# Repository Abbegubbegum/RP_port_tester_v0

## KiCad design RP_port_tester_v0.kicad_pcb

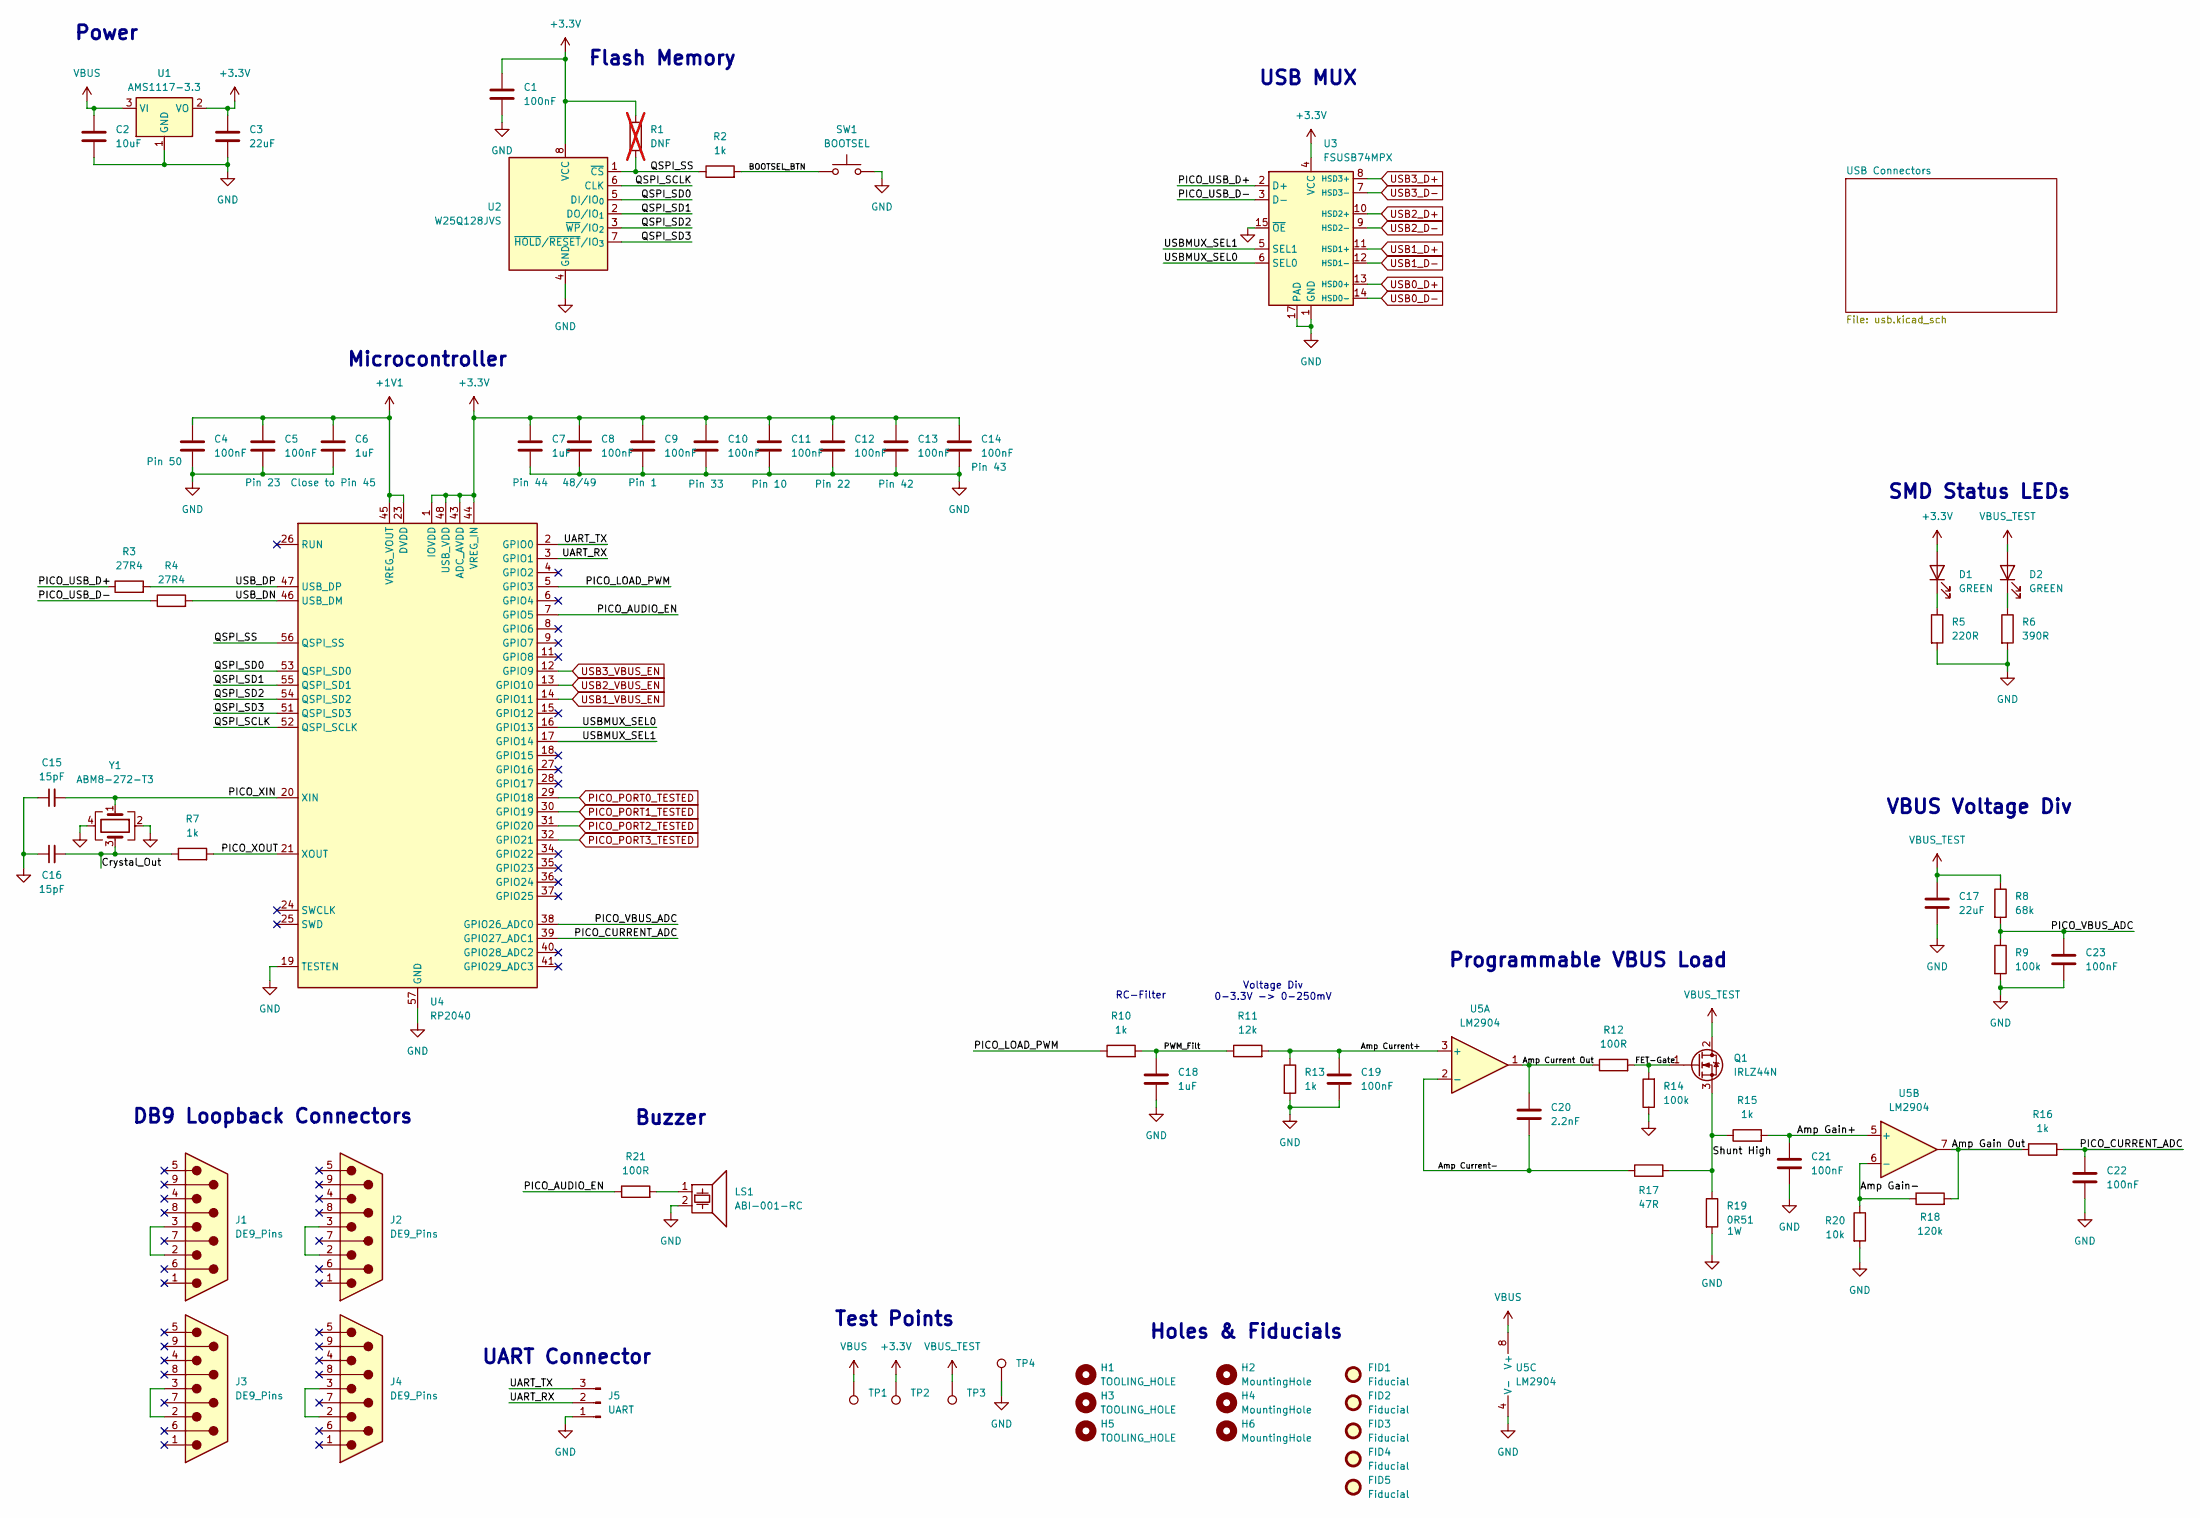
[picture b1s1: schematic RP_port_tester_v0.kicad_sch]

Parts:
C1, C4, C5, C8, C9, C10, C11, C12, C13, C14, C19, C21, C22, C23: 100nF; C_0603_1608Metric_Pad1.08x0.95mm_HandSolder
C2: 10uF; C_1206_3216Metric_Pad1.33x1.80mm_HandSolder
C3, C17: 22uF; C_1206_3216Metric_Pad1.33x1.80mm_HandSolder
C6, C7, C18: 1uF; C_0603_1608Metric_Pad1.08x0.95mm_HandSolder
C15, C16: 15pF; C_0402_1005Metric_Pad0.74x0.62mm_HandSolder
C20: 2.2nF; C_0402_1005Metric_Pad0.74x0.62mm_HandSolder
D1, D2: GREEN; D_0805_2012Metric_Pad1.15x1.40mm_HandSolder
FID1, FID2, FID3, FID4, FID5: Fiducial; Fiducial_1mm_Mask2mm
H1, H3, H5: TOOLING_HOLE; ToolingHole_1.152mm
H2, H4, H6: MountingHole; MountingHole_3.2mm_M3
J1, J2, J3, J4: DE9_Pins; DB9_Horizontal
J5: UART; PinHeader_1x03_P2.54mm_Vertical
LS1: ABI-001-RC; Buzzer_15x7.5RM7.6
Q1: IRLZ44N; TO-220-3_Horizontal_TabDown
R1: DNF; R_0603_1608Metric_Pad0.98x0.95mm_HandSolder; not fitted
R2, R7, R10, R13, R15, R16: 1k; R_0603_1608Metric_Pad0.98x0.95mm_HandSolder
R3, R4: 27R4; R_0603_1608Metric_Pad0.98x0.95mm_HandSolder
R5: 220R; R_0603_1608Metric_Pad0.98x0.95mm_HandSolder
R6: 390R; R_0603_1608Metric_Pad0.98x0.95mm_HandSolder
R8: 68k; R_0603_1608Metric_Pad0.98x0.95mm_HandSolder
R9, R14: 100k; R_0603_1608Metric_Pad0.98x0.95mm_HandSolder
R11: 12k; R_0603_1608Metric_Pad0.98x0.95mm_HandSolder
R12, R21: 100R; R_0603_1608Metric_Pad0.98x0.95mm_HandSolder
R17: 47R; R_0603_1608Metric_Pad0.98x0.95mm_HandSolder
R18: 120k; R_0603_1608Metric_Pad0.98x0.95mm_HandSolder
R19: 0R51; R_Axial_DIN0309_L9.0mm_D3.2mm_P15.24mm_Horizontal
R20: 10k; R_0603_1608Metric_Pad0.98x0.95mm_HandSolder
SW1: BOOTSEL; SW_SPST_PTS645Sx43SMTR92
TP1, TP2, TP3, TP4: TestPoint; TestPoint_Plated_Hole_D2.0mm
U1: AMS1117-3.3; SOT-223-3_TabPin2
U2: W25Q128JVS; SOIC-8_5.3x5.3mm_P1.27mm
U3: FSUSB74MPX; QFN-16-1EP_3x3mm_P0.5mm_EP1.7x1.7mm_ThermalVias
U4: RP2040; QFN-56-1EP_7x7mm_P0.4mm_EP3.2x3.2mm_ThermalVias
U5: LM2904; DIP-8_W7.62mm
Y1: ABM8-272-T3; Crystal_SMD_Abracon_ABM8G-4Pin_3.2x2.5mm

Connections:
+1V1: C4.1, C5.1, C6.1, U4.23 (DVDD), U4.45 (VREG_VOUT), U4.50 (DVDD)
+3.3V: C1.1, C3.1, C7.1, C8.1, C9.1, C10.1, C11.1, C12.1, C13.1, C14.1, D1.2 (A), R1.1, TP2.1, U1.2 (VO), U2.8 (VCC), U3.4 (VCC), U4.1 (IOVDD), U4.10 (IOVDD), U4.22 (IOVDD), U4.33 (IOVDD), U4.42 (IOVDD), U4.43 (ADC_AVDD), U4.44 (VREG_IN), U4.48 (USB_VDD), U4.49 (IOVDD)
/Amp Current Out: C20.1, R12.1, U5.1
/Amp Current+: C19.1, R11.2, R13.1, U5.3 (+)
/Amp Current-: C20.2, R17.1, U5.2 (-)
/Amp Gain Out: R16.1, R18.2, U5.7
/Amp Gain+: C21.1, R15.2, U5.5 (+)
/Amp Gain-: R18.1, R20.1, U5.6 (-)
/BOOTSEL_BTN: R2.2, SW1.1
/Crystal_Out: C16.2, R7.1, Y1.3
/FET-Gate: Q1.1 (G), R12.2, R14.2
/PICO_AUDIO_EN: R21.1, U4.7 (GPIO5)
/PICO_CURRENT_ADC: C22.1, R16.2, U4.39 (GPIO27_ADC1)
/PICO_LOAD_PWM: R10.1, U4.5 (GPIO3)
/PICO_USB_D+: R3.1, U3.2 (D+)
/PICO_USB_D-: R4.1, U3.3 (D-)
/PICO_VBUS_ADC: C23.1, R8.2, R9.1, U4.38 (GPIO26_ADC0)
/PICO_XIN: C15.2, U4.20 (XIN), Y1.1
/PICO_XOUT: R7.2, U4.21 (XOUT)
/PWM_Filt: C18.1, R10.2, R11.1
/QSPI_SCLK: U2.6 (CLK), U4.52 (QSPI_SCLK)
/QSPI_SD0: U2.5 (DI/IO_{0}), U4.53 (QSPI_SD0)
/QSPI_SD1: U2.2 (DO/IO_{1}), U4.55 (QSPI_SD1)
/QSPI_SD2: U2.3 (~WP/IO_{2}), U4.54 (QSPI_SD2)
/QSPI_SD3: U2.7 (~HOLD/~RESET/IO_{3}), U4.51 (QSPI_SD3)
/QSPI_SS: R1.2, R2.1, U2.1 (~CS), U4.56 (QSPI_SS)
/Shunt High: Q1.3 (S), R15.1, R17.2, R19.1
/UART_RX: J5.2, U4.3 (GPIO1)
/UART_TX: J5.3, U4.2 (GPIO0)
/USBMUX_SEL0: U3.6 (SEL0), U4.16 (GPIO13)
/USBMUX_SEL1: U3.5 (SEL1), U4.17 (GPIO14)
/USB_DN: R4.2, U4.46 (USB_DM)
/USB_DP: R3.2, U4.47 (USB_DP)
GND: C1.2, C2.2, C3.2, C4.2, C5.2, C6.2, C7.2, C8.2, C9.2, C10.2, C11.2, C12.2, C13.2, C14.2, C15.1, C16.1, C17.2, C18.2, C19.2, C21.2, C22.2, C23.2, J5.1, LS1.2, R5.2, R6.2, R9.2, R13.2, R14.1, R19.2, R20.2, SW1.2, TP4.1, U1.1 (GND), U2.4 (GND), U3.1 (GND), U3.15 (~OE), U3.17 (PAD), U4.19 (TESTEN), U4.57 (GND), U5.4 (V-), Y1.2, Y1.4; also elsewhere on the board
unnamed: D1.1 (K), R5.1
unnamed: D2.1 (K), R6.1
unnamed: J1.2, J1.3
unnamed: J2.2, J2.3
unnamed: J3.2, J3.3
unnamed: J4.2, J4.3
unnamed: LS1.1, R21.2
PICO_PORT0_TESTED: U4.29 (GPIO18); also elsewhere on the board
PICO_PORT1_TESTED: U4.30 (GPIO19); also elsewhere on the board
PICO_PORT2_TESTED: U4.31 (GPIO20); also elsewhere on the board
PICO_PORT3_TESTED: U4.32 (GPIO21); also elsewhere on the board
USB0_D+: U3.13 (HSD0+); also elsewhere on the board
USB0_D-: U3.14 (HSD0-); also elsewhere on the board
USB1_D+: U3.11 (HSD1+); also elsewhere on the board
USB1_D-: U3.12 (HSD1-); also elsewhere on the board
USB1_VBUS_EN: U4.14 (GPIO11); also elsewhere on the board
USB2_D+: U3.10 (HSD2+); also elsewhere on the board
USB2_D-: U3.9 (HSD2-); also elsewhere on the board
USB2_VBUS_EN: U4.13 (GPIO10); also elsewhere on the board
USB3_D+: U3.8 (HSD3+); also elsewhere on the board
USB3_D-: U3.7 (HSD3-); also elsewhere on the board
USB3_VBUS_EN: U4.12 (GPIO9); also elsewhere on the board
VBUS: C2.1, TP1.1, U1.3 (VI), U5.8 (V+); also elsewhere on the board
VBUS_TEST: C17.1, D2.2 (A), Q1.2 (D), R8.1, TP3.1; also elsewhere on the board

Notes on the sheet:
DB9 Loopback Connectors
Microcontroller
Voltage Div 0-3.3V -> 0-250mV
Programmable VBUS Load
Power
RC-Filter
SMD Status LEDs
Buzzer
Flash Memory
Holes & Fiducials
USB MUX
VBUS Voltage Div
UART Connector
Test Points

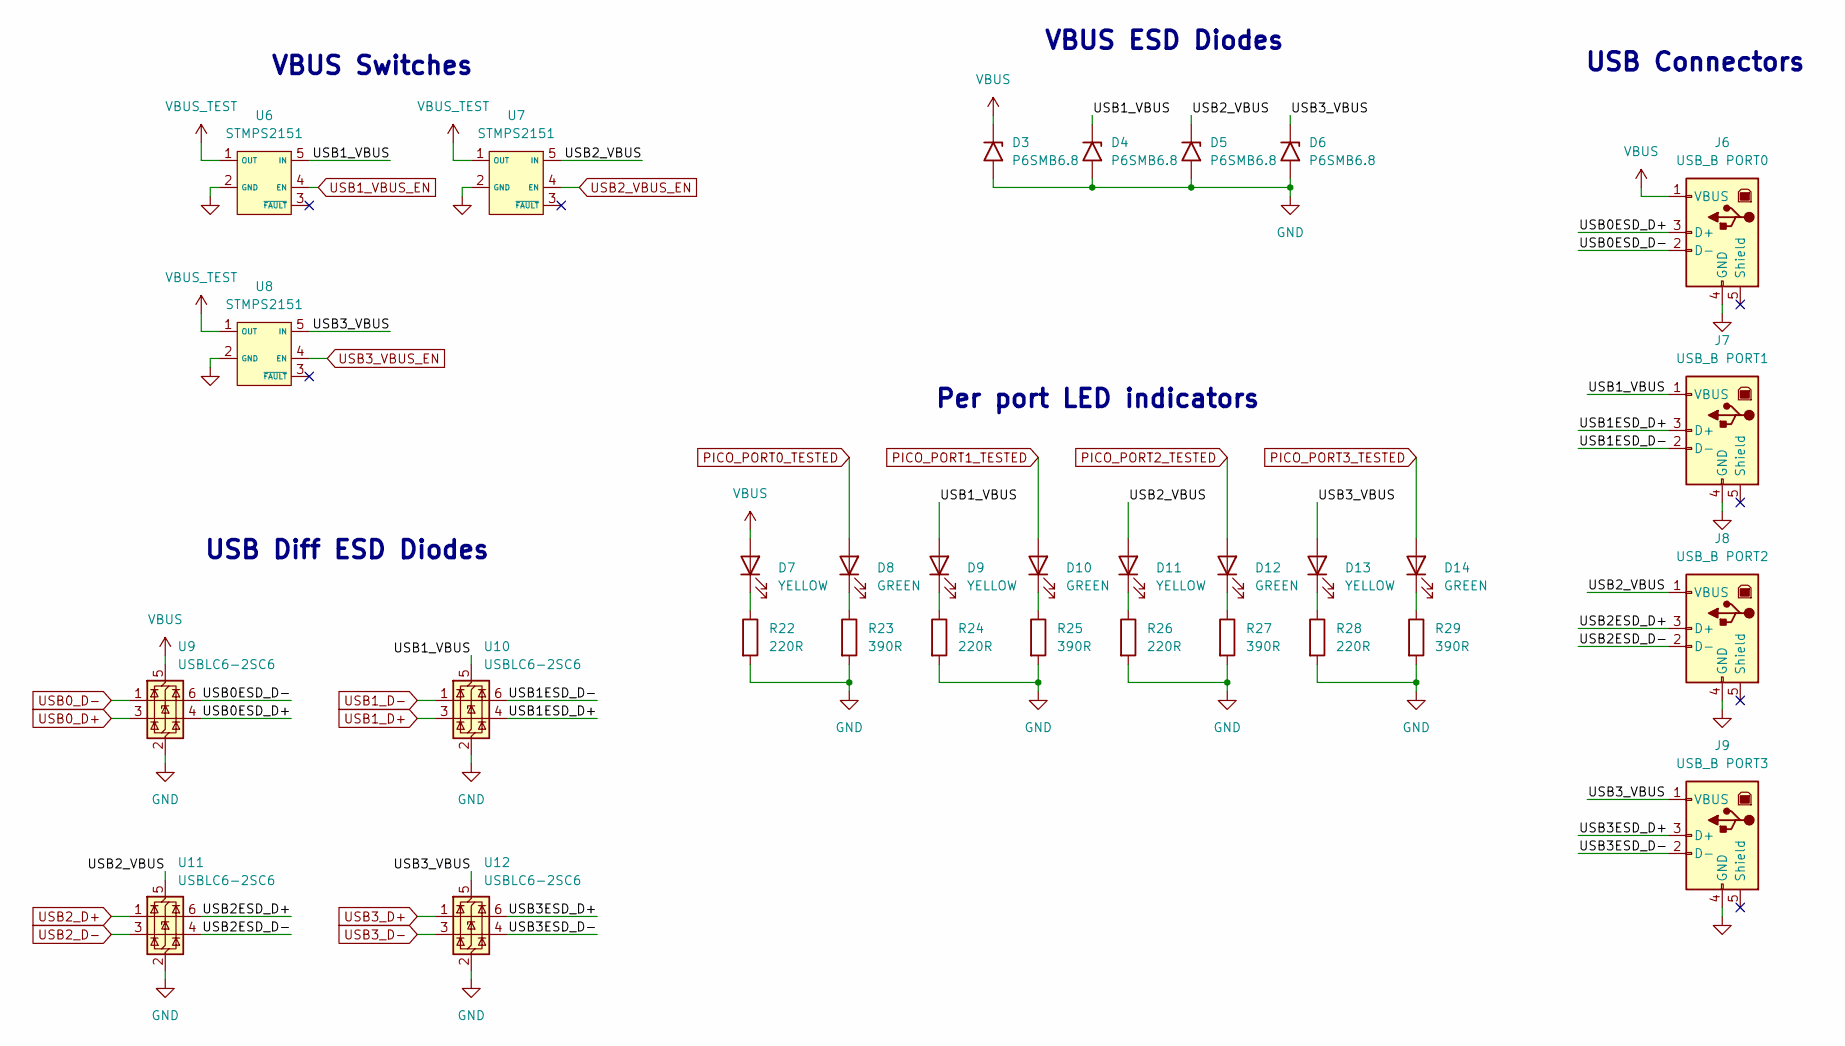
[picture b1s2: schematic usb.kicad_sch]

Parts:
D3, D4, D5, D6: P6SMB6.8; D_SMB
D7, D9, D11, D13: YELLOW; LED_D3.0mm
D8, D10, D12, D14: GREEN; LED_D3.0mm
J6: USB_B PORT0; USB_B_Vertical
J7: USB_B PORT1; USB_B_Vertical
J8: USB_B PORT2; USB_B_Vertical
J9: USB_B PORT3; USB_B_Vertical
R22, R24, R26, R28: 220R; R_0603_1608Metric_Pad0.98x0.95mm_HandSolder
R23, R25, R27, R29: 390R; R_0603_1608Metric_Pad0.98x0.95mm_HandSolder
U6, U7, U8: STMPS2151; SOT-23-5_HandSoldering
U9, U10, U11, U12: USBLC6-2SC6; SOT-23-6

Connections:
/USB Connectors/USB0ESD_D+: J6.3 (D+), U9.4 (I/O2)
/USB Connectors/USB0ESD_D-: J6.2 (D-), U9.6 (I/O1)
/USB Connectors/USB1ESD_D+: J7.3 (D+), U10.4 (I/O2)
/USB Connectors/USB1ESD_D-: J7.2 (D-), U10.6 (I/O1)
/USB Connectors/USB1_VBUS: D4.1 (A1), D9.2 (A), J7.1 (VBUS), U6.5 (IN), U10.5 (VBUS)
/USB Connectors/USB2ESD_D+: J8.3 (D+), U11.6 (I/O1)
/USB Connectors/USB2ESD_D-: J8.2 (D-), U11.4 (I/O2)
/USB Connectors/USB2_VBUS: D5.1 (A1), D11.2 (A), J8.1 (VBUS), U7.5 (IN), U11.5 (VBUS)
/USB Connectors/USB3ESD_D+: J9.3 (D+), U12.6 (I/O1)
/USB Connectors/USB3ESD_D-: J9.2 (D-), U12.4 (I/O2)
/USB Connectors/USB3_VBUS: D6.1 (A1), D13.2 (A), J9.1 (VBUS), U8.5 (IN), U12.5 (VBUS)
GND: D3.2 (A2), D4.2 (A2), D5.2 (A2), D6.2 (A2), J6.4 (GND), J7.4 (GND), J8.4 (GND), J9.4 (GND), R22.2, R23.2, R24.2, R25.2, R26.2, R27.2, R28.2, R29.2, U6.2 (GND), U7.2 (GND), U8.2 (GND), U9.2 (GND), U10.2 (GND), U11.2 (GND), U12.2 (GND); also elsewhere on the board
unnamed: D7.1 (K), R22.1
unnamed: D8.1 (K), R23.1
unnamed: D9.1 (K), R24.1
unnamed: D10.1 (K), R25.1
unnamed: D11.1 (K), R26.1
unnamed: D12.1 (K), R27.1
unnamed: D13.1 (K), R28.1
unnamed: D14.1 (K), R29.1
PICO_PORT0_TESTED: D8.2 (A); also elsewhere on the board
PICO_PORT1_TESTED: D10.2 (A); also elsewhere on the board
PICO_PORT2_TESTED: D12.2 (A); also elsewhere on the board
PICO_PORT3_TESTED: D14.2 (A); also elsewhere on the board
USB0_D+: U9.3 (I/O2); also elsewhere on the board
USB0_D-: U9.1 (I/O1); also elsewhere on the board
USB1_D+: U10.3 (I/O2); also elsewhere on the board
USB1_D-: U10.1 (I/O1); also elsewhere on the board
USB1_VBUS_EN: U6.4 (EN); also elsewhere on the board
USB2_D+: U11.1 (I/O1); also elsewhere on the board
USB2_D-: U11.3 (I/O2); also elsewhere on the board
USB2_VBUS_EN: U7.4 (EN); also elsewhere on the board
USB3_D+: U12.1 (I/O1); also elsewhere on the board
USB3_D-: U12.3 (I/O2); also elsewhere on the board
USB3_VBUS_EN: U8.4 (EN); also elsewhere on the board
VBUS: D3.1 (A1), D7.2 (A), J6.1 (VBUS), U9.5 (VBUS); also elsewhere on the board
VBUS_TEST: U6.1 (OUT), U7.1 (OUT), U8.1 (OUT); also elsewhere on the board

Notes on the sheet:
VBUS ESD Diodes
USB Diff ESD Diodes
VBUS Switches
Per port LED indicators
USB Connectors

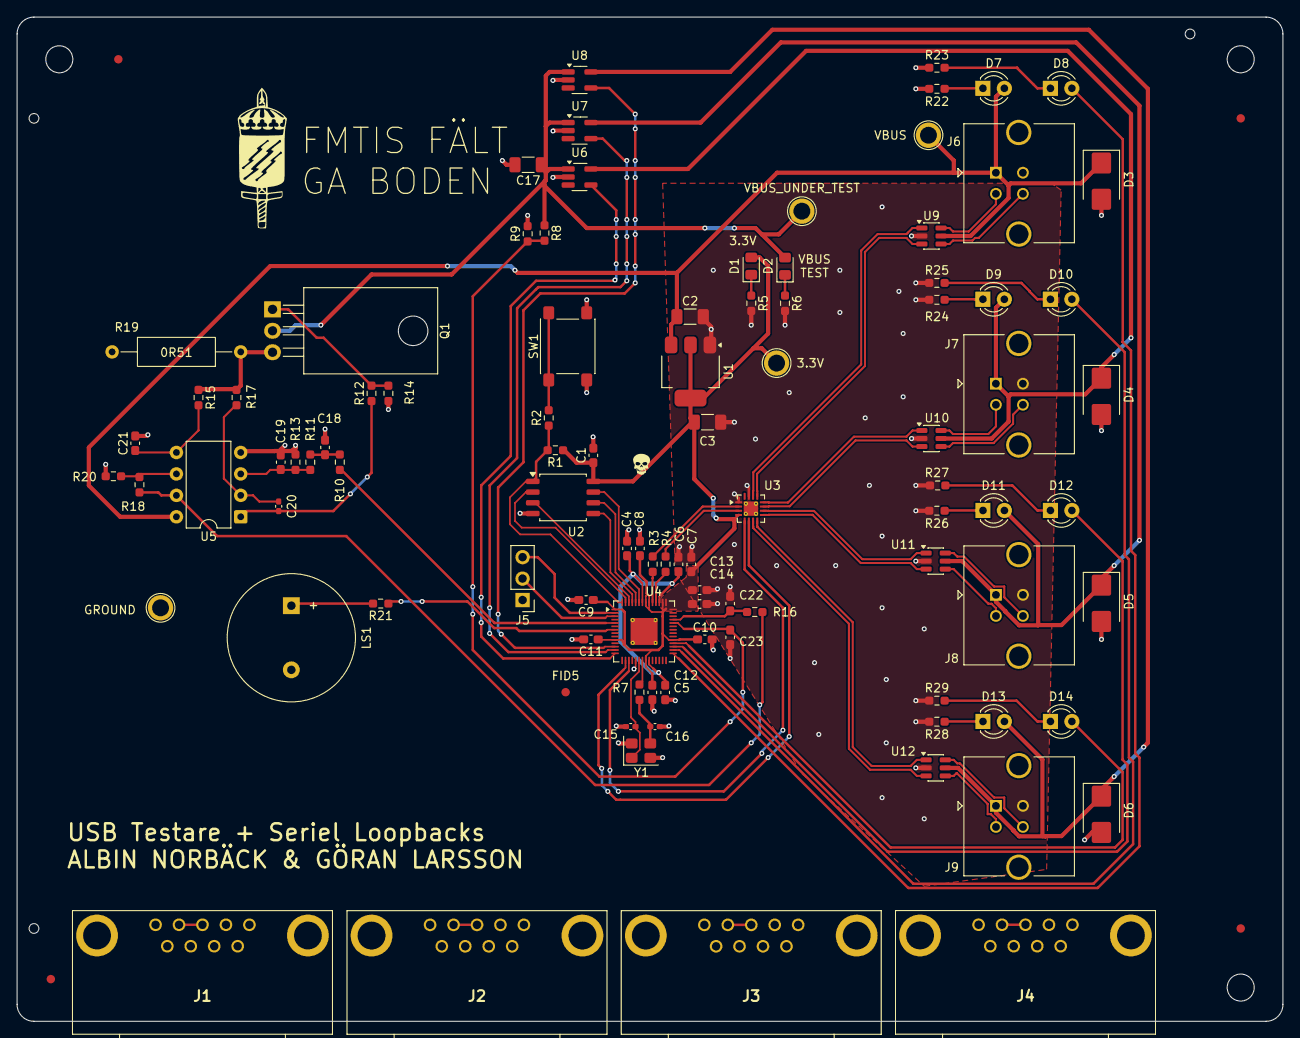
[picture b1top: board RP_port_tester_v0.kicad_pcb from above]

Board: 2 copper layers, 150.0 x 119.0 mm, 106 parts (0 on the bottom side), 77 nets.

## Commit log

2025-10-15 Initial Schematic and component selection
2025-10-16 Layout and Tracing
2025-10-20 Final layout and routing
2025-10-20 Fix DB9 port misalignment
